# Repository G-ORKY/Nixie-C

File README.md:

This is the Nixie pipe clock reated by GORKY with special driver moduel or hv57708pg.
The project file generated by KiCad will be uploaded after all the software and hardware contents are tested and be confirmed to be safe and stable for use.
As planned, it will take at least 6 months for this project to be completed due to my tight schedule and poor ability.
If you have any better solutions, please contact me.

This is a project depend on ESP32-S3-MINI-1U, which is a control module with WI-FI and Bluetooth comprised.
In plan, it will use a special designed USB connector on the pcb instead of the outside USB-C connector to avoid the system damage by accident.

Pcb files in 'Nixie', and some symbols and footprints files you may need are in folder 'Symbols&footprints'

空的！空的！全完啦
主包开摆了（
看心情画板子了以后

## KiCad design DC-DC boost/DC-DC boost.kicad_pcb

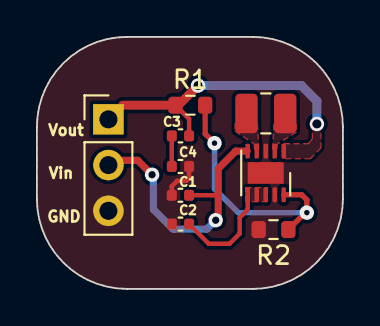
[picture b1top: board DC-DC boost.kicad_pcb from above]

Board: 2 copper layers, 17.0 x 14.0 mm, 9 parts (0 on the bottom side), 8 nets.

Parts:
C1, C2, C3, C4: C; C_0402_1005Metric
FTC252012S1R5MBCA1: 1.5uH; L_1008_2520Metric
J1: Conn_01x03; PinHeader_1x03_P2.54mm_Vertical
R1: 2.8M; R_0603_1608Metric
R2: 500K; R_0603_1608Metric
U1: TPS63030DSK; WSON-10-1EP_2.5x2.5mm_P0.5mm_EP1.2x2mm

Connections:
unnamed: C3.2, C4.1
unnamed: C3.1, J1.1, R1.1, U1.1 (VOUT)
unnamed: C1.1, J1.2, U1.5 (VIN)
unnamed: C1.2, C2.2, C4.2, J1.3, R2.2, U1.3 (PGND), U1.9 (GND), U1.11 (PGND)
unnamed: C2.1, U1.6 (EN), U1.7 (PS/SYNC), U1.8 (VINA)
unnamed: R1.2, R2.1, U1.10 (FB)
unnamed: FTC252012S1R5MBCA1.1, U1.4 (L1)
unnamed: FTC252012S1R5MBCA1.2, U1.2 (L2)

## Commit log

2024-05-30 First
2024-07-20 Finished DC-DC power for logic components
2024-07-23 change the layout of the 3.3v-out module
